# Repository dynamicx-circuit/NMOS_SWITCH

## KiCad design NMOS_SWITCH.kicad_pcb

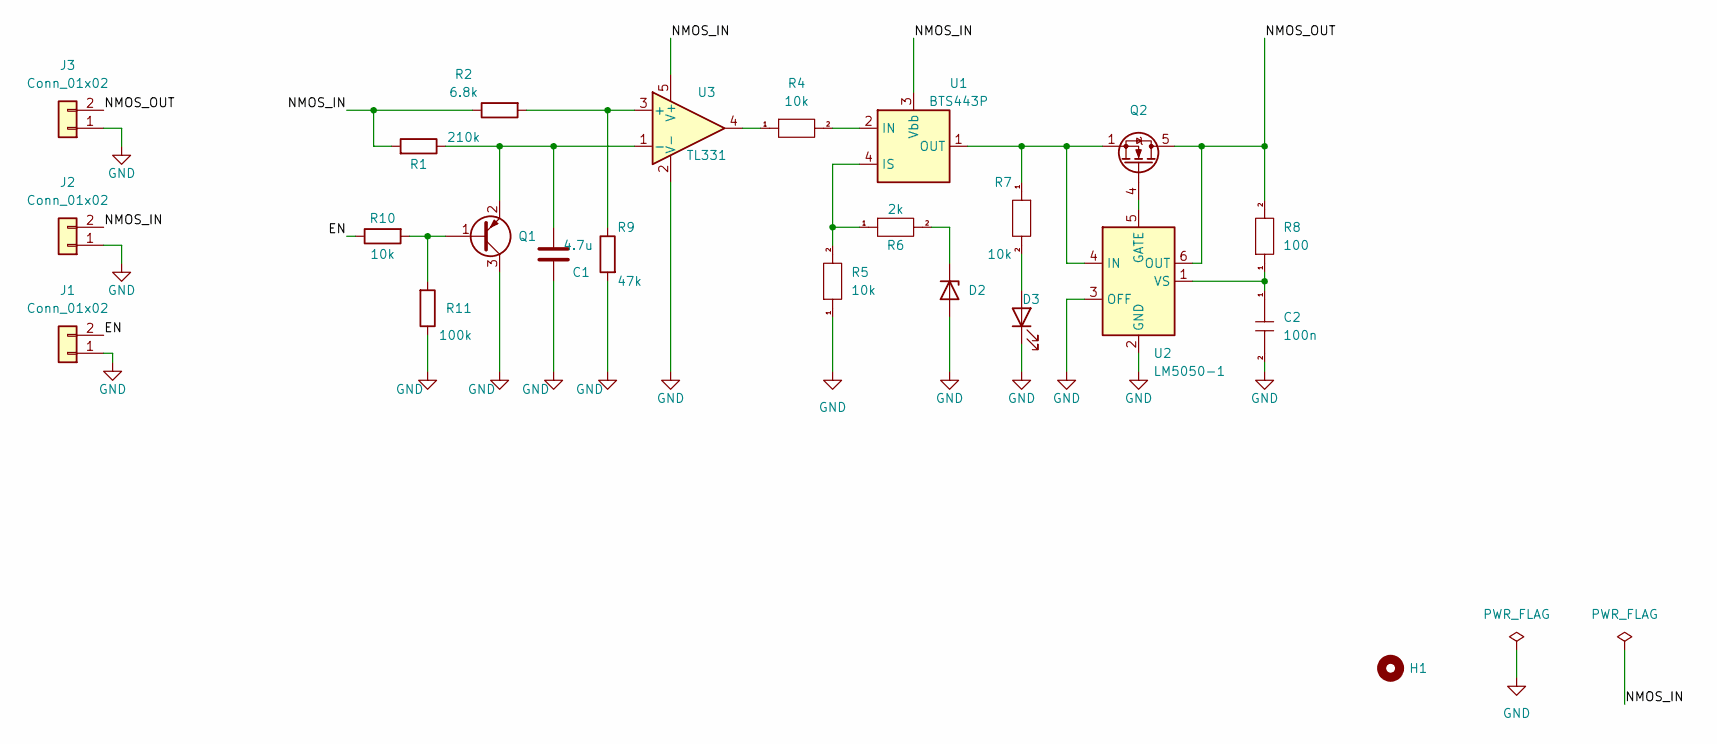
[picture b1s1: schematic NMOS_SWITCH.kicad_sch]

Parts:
C1: 4.7u; C_0805_2012Metric
C2: 100n; C_0402_1005Metric
D2: BZT52Bxx; D_SOD-123F
D3: LED; LED_0603_1608Metric
H1: MountingHole; MountingHole_3.2mm_M3
J1: Conn_01x02; AMASS_XT30UPB-M_1x02_P5.0mm_Vertical
J2: Conn_01x02; AMASS_XT60-M_1x02_P7.20mm_Vertical
J3: Conn_01x02; AMASS_XT60-F_1x02_P7.20mm_Vertical
Q1: Q_PNP_BEC; SOT-23
Q2: CSD18540Q5B; TDSON-8-1
R1: 210k; R_0402_1005Metric
R2: 6.8k; R_0402_1005Metric
R4, R5, R7, R10: 10k; R_0402_1005Metric
R6: 2k; R_0402_1005Metric
R8: 100; R_0402_1005Metric
R9: 47k; R_0402_1005Metric
R11: 100k; R_0402_1005Metric
U1: BTS443P; TO-252-4
U2: LM5050-1; TSOT-23-6
U3: TL331; SOT-23-5

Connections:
/EN: J1.2, R10.1
/NMOS_IN: J2.2, R1.2, R2.1, U1.3 (Vbb), U3.5 (V+)
/NMOS_OUT: J3.2, Q2.5 (D), R8.2, U2.6 (OUT)
GND: C1.2, C2.2, D2.2 (A), D3.1 (K), J1.1, J2.1, J3.1, Q1.3 (C), R5.1, R9.2, R11.1, U2.2 (GND), U2.3 (OFF), U3.2 (V-)
unnamed: D2.1 (K), R6.2
unnamed: D3.2 (A), R7.2
unnamed: Q2.1 (S), Q2.2 (S), Q2.3 (S), R7.1, U1.1 (OUT), U1.5 (OUT), U2.4 (IN)
unnamed: R4.1, U3.4
unnamed: R4.2, U1.2 (IN)
unnamed: R5.2, R6.1, U1.4 (IS)
unnamed: Q1.1 (B), R10.2, R11.2
unnamed: C2.1, R8.1, U2.1 (VS)
unnamed: Q2.4 (G), U2.5 (GATE)
unnamed: C1.1, Q1.2 (E), R1.1, U3.1 (-)
unnamed: R2.2, R9.1, U3.3 (+)

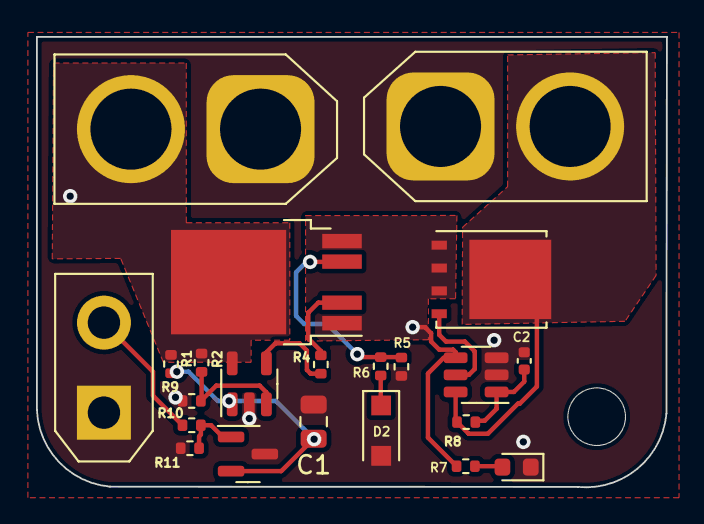
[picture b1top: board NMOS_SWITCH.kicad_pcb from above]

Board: 2 copper layers, 35.0 x 25.0 mm, 23 parts (0 on the bottom side), 15 nets.

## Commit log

2022-10-19 Add time delay
2023-03-11 Use LM5060, and update PCB
2023-03-11 Change .gitignore
